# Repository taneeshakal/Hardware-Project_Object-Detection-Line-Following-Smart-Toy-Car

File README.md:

# Hardware-Project_Object-Detection-Line-Following-Smart-Toy-Car

##Project description

Mainly this car will be able to follow a black line drawn by the child in a white paper or any white 
colour surface, with the use of two IR sensors. To make the car move, go forward, backward, left 
and right, four servo motors will be used for the four wheels. A motor driver will be used to drive 
the four motors. When the car turns left or right LEDs will work as signal lights, indicating the 
turning directions.
This toy car will also be able to detect objects in its path (on the black line), with the use of an 
ultrasonic sensor. If an object is detected on the black line, the car will be automatically stopped 
and a buzzer will ring, alerting the child to remove the object from the path. Once the object is 
removed car will start moving along the line again. 
Aside from the automatic line following and object detection function, this car will also be able to 
use as a remotely controlled car, by the mobile phone with the use of a Bluetooth module.

##Other

Programming language:C,
IDE:Atmel studio
Simulation:Proteus
PCB design:Kicad

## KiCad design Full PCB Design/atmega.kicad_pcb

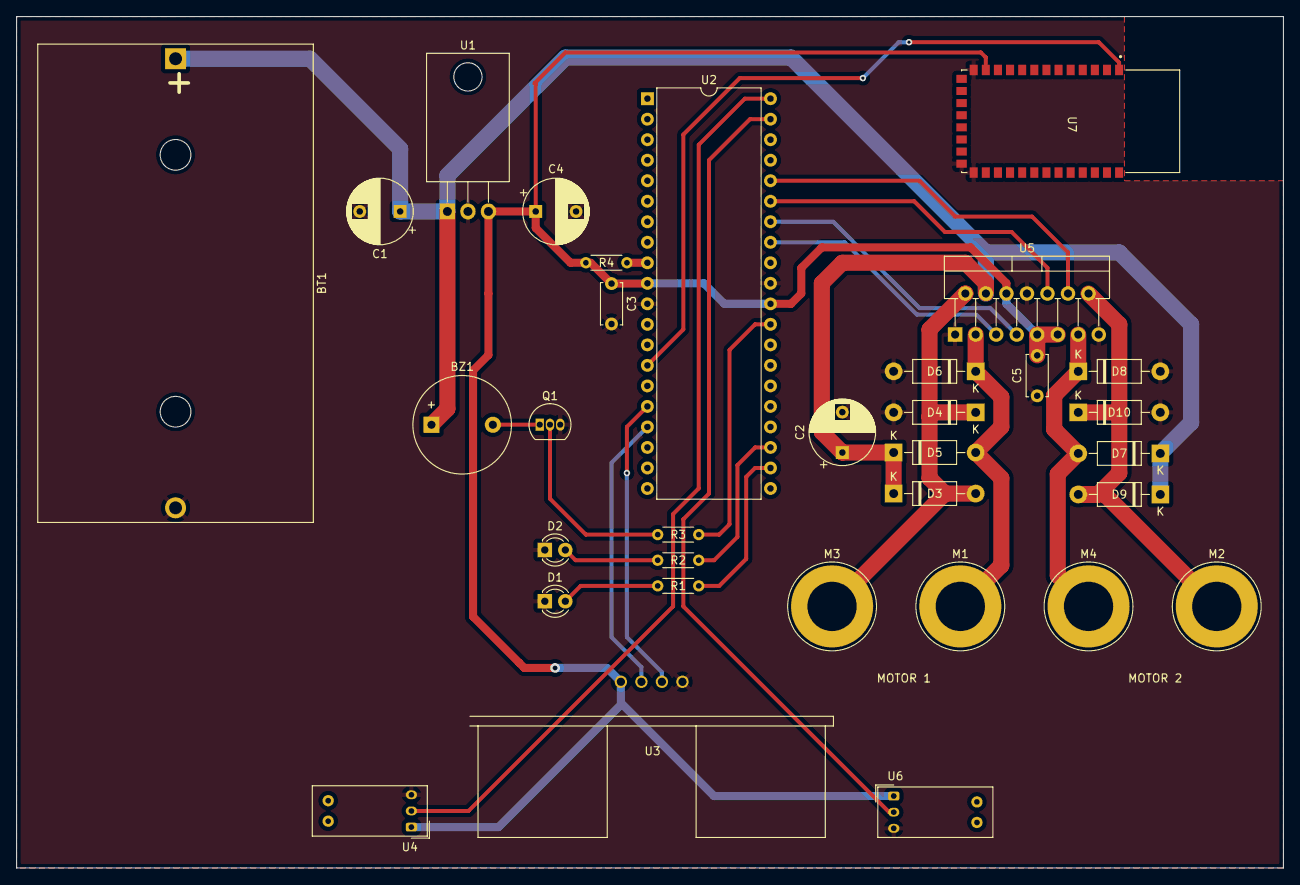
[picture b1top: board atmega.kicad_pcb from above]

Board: 2 copper layers, 156.8 x 105.4 mm, 33 parts (0 on the bottom side), 24 nets.

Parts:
BT1: Li-ion 12V Battery; BatteryHolder_Bulgin_BX0036_1xC
BZ1: Buzzer; Buzzer_12x9.5RM7.6
C1, C2, C4: 100uF/25V; CP_Radial_D8.0mm_P5.00mm
C3, C5: 0.1uF; C_Disc_D5.0mm_W2.5mm_P5.00mm
D1, D2: LED; LED_D3.0mm
D3, D4, D5, D6, D7, D8, D9, D10: 1N4001; D_DO-41_SOD81_P10.16mm_Horizontal
M1, M2, M3, M4: Motor_DC; Banana_Jack_1Pin
Q1: BC547; TO-92_Inline
R1, R2: 220; R_Axial_DIN0204_L3.6mm_D1.6mm_P5.08mm_Horizontal
R3: 1K; R_Axial_DIN0204_L3.6mm_D1.6mm_P5.08mm_Horizontal
R4: 10K; R_Axial_DIN0204_L3.6mm_D1.6mm_P5.08mm_Horizontal
U1: L7805_regulator; TO-220-3_Horizontal_TabDown
U2: ATmega32-16P; DIP-40_W15.24mm
U3: HC-SR04_ultrasonic_sensor; SR04
U4: IR_sensor1; Kodenshi_LG206L
U5: L298N; TO-220-15_P2.54x2.54mm_StaggerOdd_Lead4.58mm_Vertical
U6: IR_sensor2; Kodenshi_LG206L
U7: HC-05_bluetooth_module; HC05

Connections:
+5V: C3.1, C4.1, C5.2, R4.2, U1.3 (OUT), U2.10 (VCC), U2.30 (AVCC), U3.1 (VCC), U4.1 (VCC), U5.6 (EnA), U5.9 (Vss), U5.11 (EnB), U6.1 (VCC), U7.12 (3.3_VCC)
+12V: BT1.1 (+), BZ1.1 (-), C1.1, C2.1, D3.1 (K), D5.1 (K), D7.1 (K), D9.1 (K), U1.1 (IN), U5.4 (Vs)
GND: BT1.2 (-), C1.2, C2.2, C3.2, C4.2, C5.1, D1.1 (K), D2.1 (K), D4.2 (A), D6.2 (A), D8.2 (A), D10.2 (A), Q1.3 (E), U1.2 (GND), U2.11 (GND), U2.31 (GND), U3.4 (GND), U4.3 (GND), U5.1 (SENSE_A), U5.8 (GND), U5.15 (SENSE_B), U6.3 (GND), U7.13 (GND), U7.21 (GND), U7.22 (GND)
unnamed: BZ1.2 (+), Q1.1 (C)
unnamed: D1.2 (A), R1.2
unnamed: D2.2 (A), R2.2
unnamed: D3.2 (A), D4.1 (K), M3.1 (+), U5.2 (OUT1)
unnamed: D5.2 (A), D6.1 (K), M1.1 (+), U5.3 (OUT2)
unnamed: D7.2 (A), D8.1 (K), M4.1 (+), U5.13 (OUT3)
unnamed: D9.2 (A), D10.1 (K), M2.1 (+), U5.14 (OUT4)
unnamed: Q1.2 (B), R3.2
unnamed: R1.1, U2.22 (PC0)
unnamed: R2.1, U2.23 (PC1)
unnamed: R3.1, U2.29 (PC7)
unnamed: R4.1, U2.9 (~RESET)
unnamed: U2.14 (PD0), U7.1 (UART-TX)
unnamed: U2.16 (PD2), U3.3 (ECHO)
unnamed: U2.17 (PD3), U3.2 (TRIG)
unnamed: U2.33 (PA7), U5.5 (IN1)
unnamed: U2.34 (PA6), U5.7 (IN2)
unnamed: U2.35 (PA5), U5.10 (IN3)
unnamed: U2.36 (PA4), U5.12 (IN4)
unnamed: U2.39 (PA1), U6.2 (VOUT)
unnamed: U2.40 (PA0), U4.2 (VOUT)

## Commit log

2023-05-05 adding files
